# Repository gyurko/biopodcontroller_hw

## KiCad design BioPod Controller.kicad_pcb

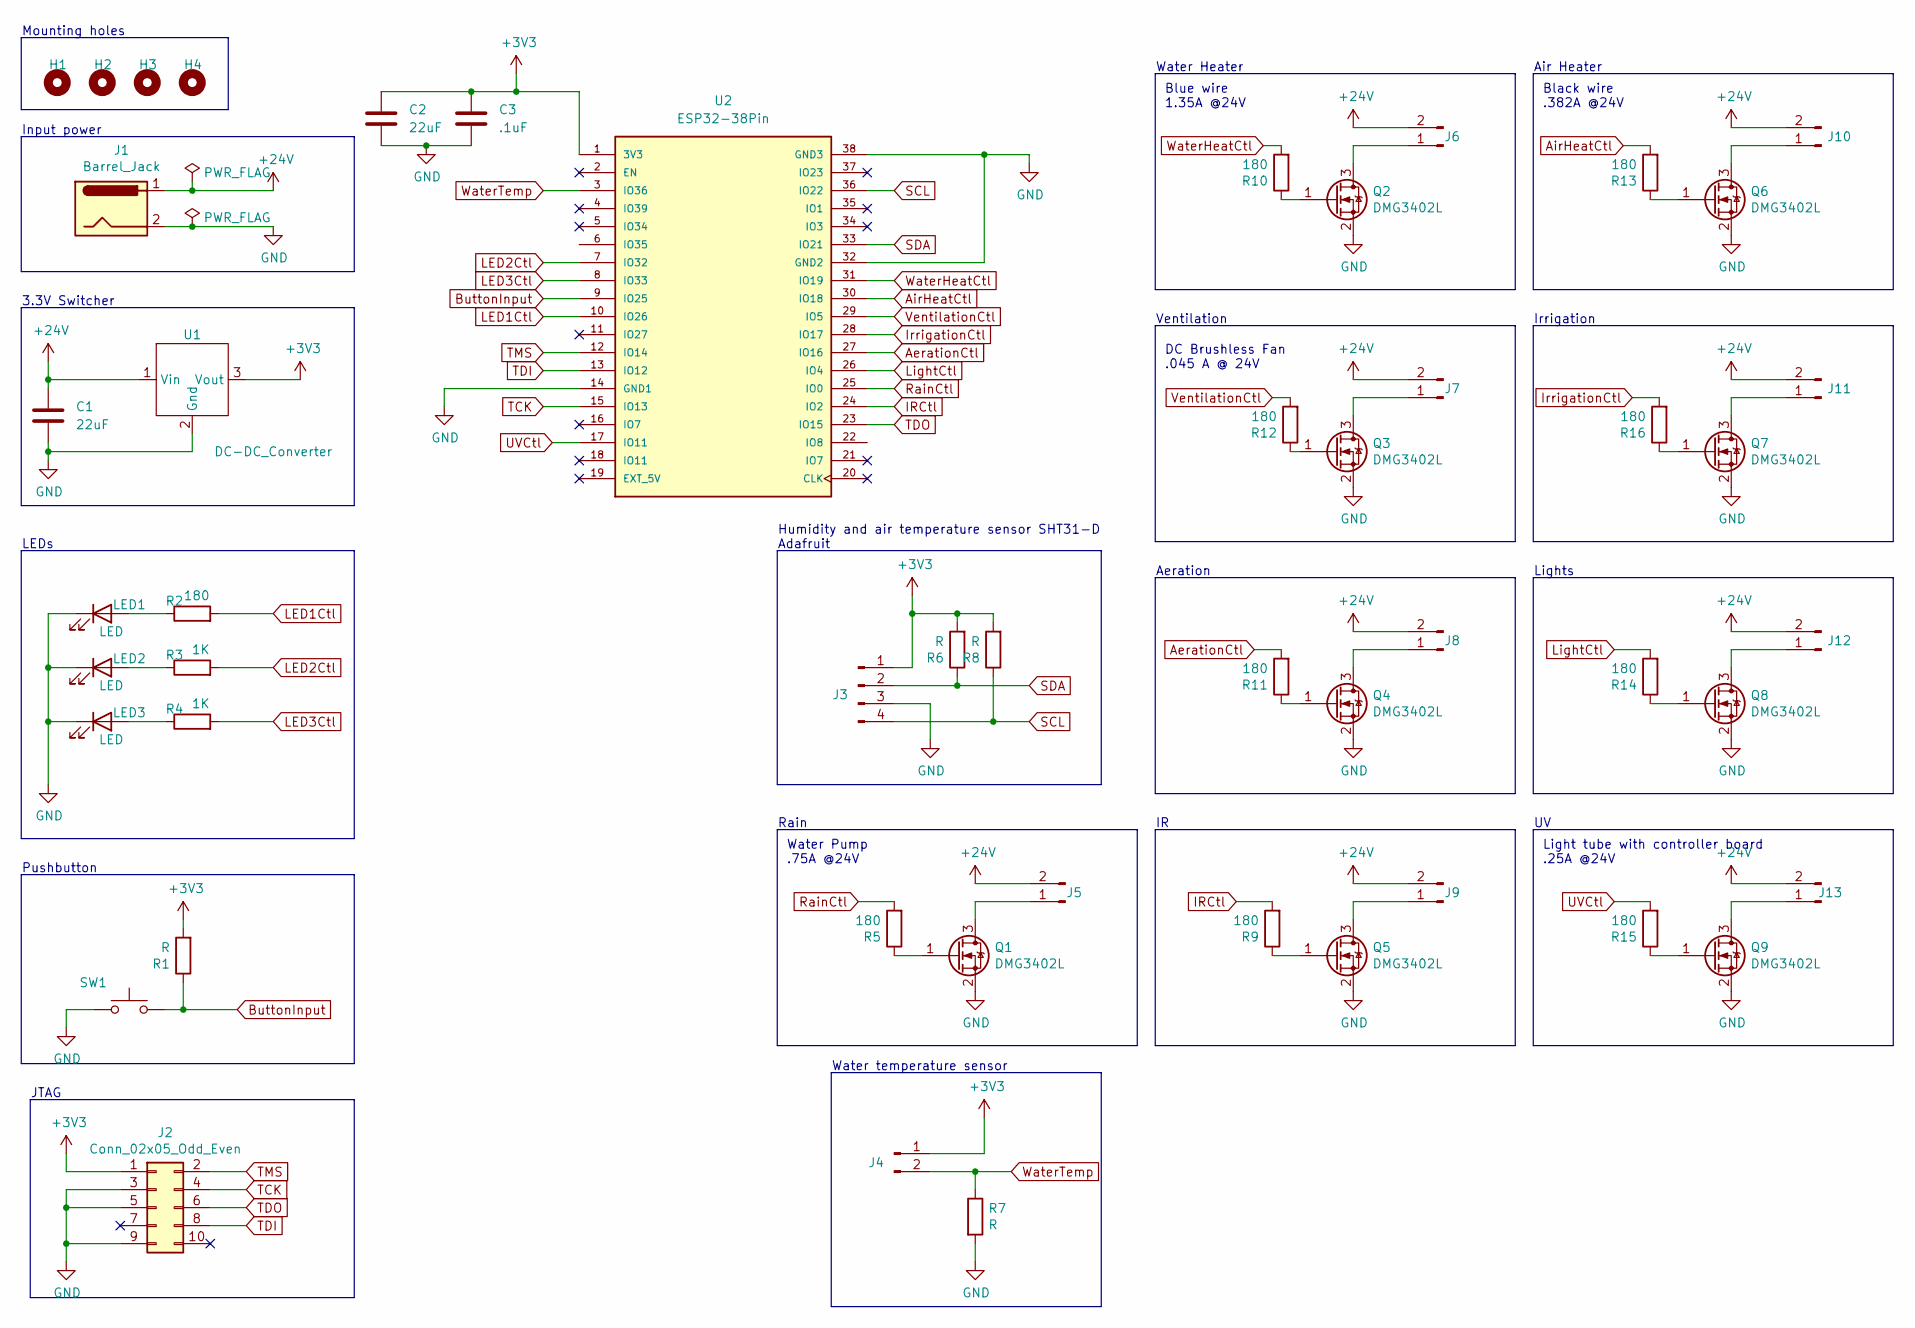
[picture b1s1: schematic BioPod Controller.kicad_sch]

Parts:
C1, C2: 22uF; C_0603_1608Metric_Pad1.08x0.95mm_HandSolder
C3: .1uF; C_0603_1608Metric_Pad1.08x0.95mm_HandSolder
H1, H2, H3, H4: MountingHole; MountingHole_3.5mm
J1: Barrel_Jack; BarrelJack_CUI_PJ-102AH_Horizontal
J2: Conn_02x05_Odd_Even; IDC-Header_2x05_P2.54mm_Vertical
J3: Conn_01x04_Male; JST_EH_B4B-EH-A_1x04_P2.50mm_Vertical
J4, J5, J6, J7, J8, J9, J10, J11, J12, J13: Conn_01x02_Male; JST_EH_B2B-EH-A_1x02_P2.50mm_Vertical
LED1, LED2, LED3: LED; LED_0603_1608Metric_Pad1.05x0.95mm_HandSolder
Q1, Q2, Q3, Q4, Q5, Q6, Q7, Q8, Q9: DMG3402L; SOT-23
R1, R6, R7, R8: R; R_0603_1608Metric_Pad0.98x0.95mm_HandSolder
R2, R5, R9, R10, R11, R12, R13, R14, R15, R16: 180; R_0603_1608Metric_Pad0.98x0.95mm_HandSolder
R3, R4: 1K; R_0603_1608Metric_Pad0.98x0.95mm_HandSolder
SW1: SW_Push; BiopodPushbutton
U1: DC-DC_Converter; DC_DC_Converter
U2: ESP32-38Pin; DIP-38_1000; PARTREV 4

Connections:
+3V3: C2.1, C3.1, J2.1, J3.1, J4.1, R1.2, R6.2, R8.2, U1.3 (Vout), U2.1 (3V3)
+24V: C1.1, J1.1, J5.2, J6.2, J7.2, J8.2, J9.2, J10.2, J11.2, J12.2, J13.2, U1.1 (Vin)
AerationCtl: R11.2, U2.27 (IO16)
AirHeatCtl: R13.2, U2.30 (IO18)
ButtonInput: R1.1, SW1.2, U2.9 (IO25)
GND: C1.2, C2.2, C3.2, J1.2, J2.3, J2.5, J2.9, J3.3, LED1.1 (K), LED2.1 (K), LED3.1 (K), Q1.2 (S), Q2.2 (S), Q3.2 (S), Q4.2 (S), Q5.2 (S), Q6.2 (S), Q7.2 (S), Q8.2 (S), Q9.2 (S), R7.2, SW1.1, U1.2 (Gnd), U2.14 (GND1), U2.32 (GND2), U2.38 (GND3)
IRCtl: R9.2, U2.24 (IO2)
IrrigationCtl: R16.2, U2.28 (IO17)
LED1Ctl: R2.2, U2.10 (IO26)
LED2Ctl: R3.2, U2.7 (IO32)
LED3Ctl: R4.2, U2.8 (IO33)
LightCtl: R14.2, U2.26 (IO4)
unnamed: J5.1, Q1.3 (D)
unnamed: J6.1, Q2.3 (D)
unnamed: J7.1, Q3.3 (D)
unnamed: J8.1, Q4.3 (D)
unnamed: J9.1, Q5.3 (D)
unnamed: J10.1, Q6.3 (D)
unnamed: J11.1, Q7.3 (D)
unnamed: J12.1, Q8.3 (D)
unnamed: J13.1, Q9.3 (D)
unnamed: LED1.2 (A), R2.1
unnamed: LED2.2 (A), R3.1
unnamed: LED3.2 (A), R4.1
unnamed: Q1.1 (G), R5.1
unnamed: Q2.1 (G), R10.1
unnamed: Q3.1 (G), R12.1
unnamed: Q4.1 (G), R11.1
unnamed: Q5.1 (G), R9.1
unnamed: Q6.1 (G), R13.1
unnamed: Q7.1 (G), R16.1
unnamed: Q8.1 (G), R14.1
unnamed: Q9.1 (G), R15.1
RainCtl: R5.2, U2.25 (IO0)
SCL: J3.4, R8.1, U2.36 (IO22)
SDA: J3.2, R6.1, U2.33 (IO21)
TCK: J2.4, U2.15 (IO13)
TDI: J2.8, U2.13 (IO12)
TDO: J2.6, U2.23 (IO15)
TMS: J2.2, U2.12 (IO14)
UVCtl: R15.2, U2.17 (IO11), U2.22 (IO8)
VentilationCtl: R12.2, U2.29 (IO5)
WaterHeatCtl: R10.2, U2.31 (IO19)
WaterTemp: J4.2, R7.1, U2.3 (IO36)

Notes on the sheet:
Mounting holes
Air Heater
Black wire .382A @24V
Light tube with controller board .25A @24V
Pushbutton
Lights
Rain
Humidity and air temperature sensor SHT31-D Adafruit
DC Brushless Fan .045 A @ 24V
Input power
Water temperature sensor
Water Heater
JTAG
Blue wire 1.35A @24V
3.3V Switcher
LEDs
Water Pump .75A @24V
Aeration
Ventilation
Irrigation

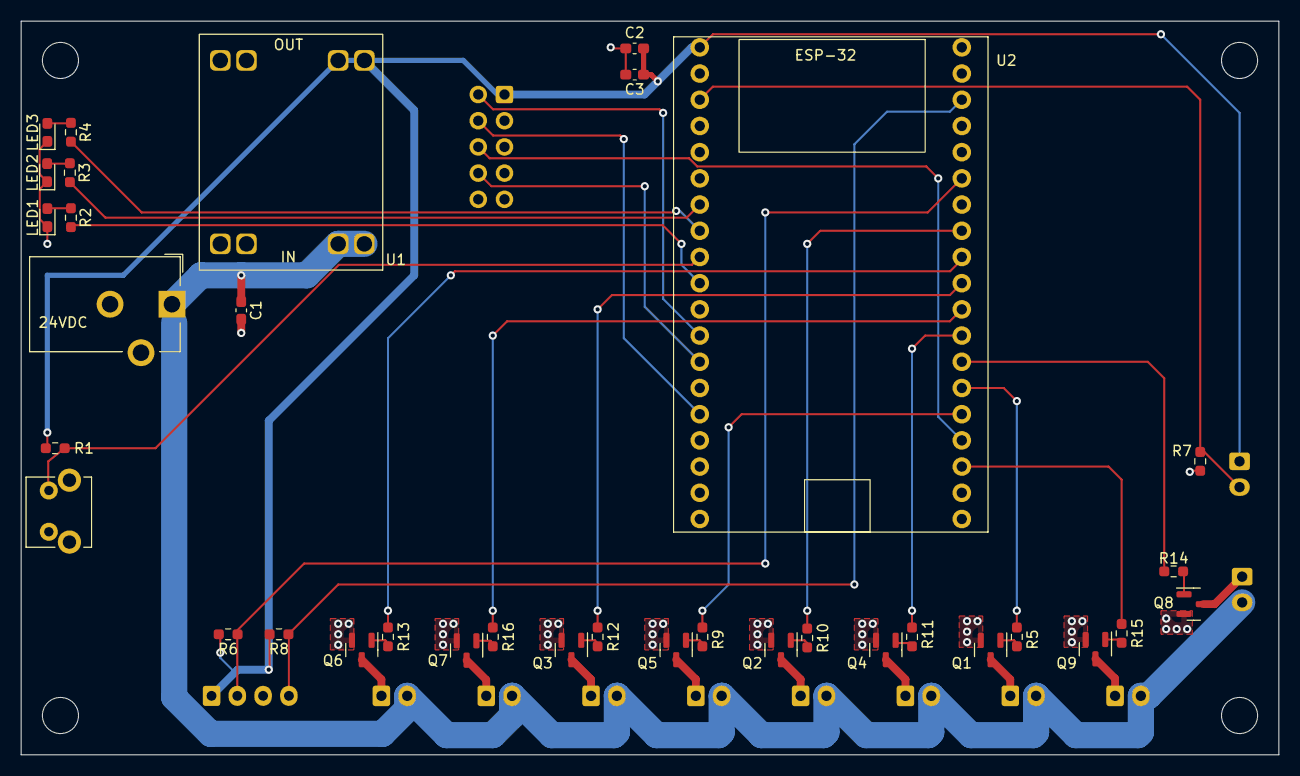
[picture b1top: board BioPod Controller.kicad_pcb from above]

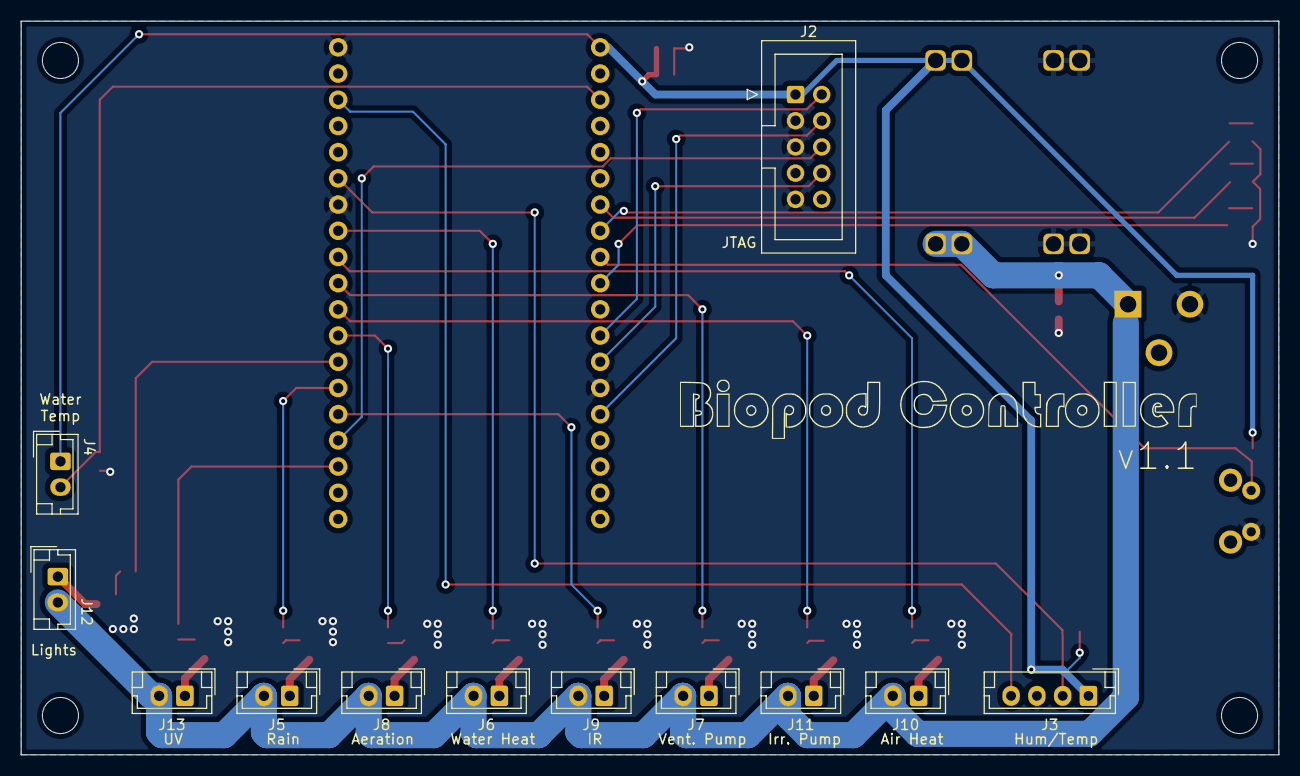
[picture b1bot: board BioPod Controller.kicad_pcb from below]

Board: 2 copper layers, 121.9 x 71.1 mm, 51 parts (12 on the bottom side), 44 nets.
